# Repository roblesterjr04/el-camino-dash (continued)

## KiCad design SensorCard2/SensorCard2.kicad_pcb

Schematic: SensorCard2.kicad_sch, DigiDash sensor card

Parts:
C1, C5: 10u; C_0805_2012Metric
C2, C3, C4, C6, C7, C9, C10, C12, C13, C14, C15, C16, C21: 100n; C_0603_1608Metric
C8: 4.7u; C_0805_2012Metric
C17, C18, C19, C20: 10n; C_0603_1608Metric
C22: 100n; C_0805_2012Metric
C23, C24: 1n; C_0603_1608Metric
D1, D4, D5, D6, D7, D8, D9, D10: BAT54S; SOT-23
D2: BAT42W; D_SOD-123
D3: green; LED_0603_1608Metric
D11: 1N4148W; D_SOD-123
F1, F2, F3: PTC 0.1A; Fuse_1206_3216Metric
J1: DigiDash slot; PinHeader_2x15_P2.54mm_Horizontal
J2: Senders; JST_PH_S12B-PH-K_1x12_P2.00mm_Horizontal
J3: Speed; JST_PH_S4B-PH-K_1x04_P2.00mm_Horizontal
J4: Tach; Molex_Micro-Fit_3.0_43650-0200_1x02_P3.00mm_Horizontal
J5: RPM select; PinHeader_2x02_P2.54mm_Vertical
J6: SWD; PinHeader_1x05_P2.54mm_Horizontal
J7: Debug serial; PinHeader_1x06_P2.54mm_Horizontal
J8: Sensor serial out; PinHeader_1x03_P2.54mm_Horizontal
JP1: 5V / 12V; SolderJumper-3_P1.3mm_Bridged12_RoundedPad1.0x1.5mm
JP2: FUEL PU / PD; SolderJumper-3_P1.3mm_Bridged12_RoundedPad1.0x1.5mm
JP3: ETEMP PU / PD; SolderJumper-3_P1.3mm_Bridged12_RoundedPad1.0x1.5mm
JP4: OILP PU / PD; SolderJumper-3_P1.3mm_Bridged12_RoundedPad1.0x1.5mm
JP5: AMB PU / PD; SolderJumper-3_P1.3mm_Bridged12_RoundedPad1.0x1.5mm
JP6: FUEL 100; SolderJumper-2_P1.3mm_Bridged_RoundedPad1.0x1.5mm
JP7: FUEL 220; SolderJumper-2_P1.3mm_Open_RoundedPad1.0x1.5mm
JP8: FUEL 470; SolderJumper-2_P1.3mm_Open_RoundedPad1.0x1.5mm
JP9: ETEMP 220; SolderJumper-2_P1.3mm_Open_RoundedPad1.0x1.5mm
JP10: ETEMP 1k; SolderJumper-2_P1.3mm_Bridged_RoundedPad1.0x1.5mm
JP11: ETEMP 10k; SolderJumper-2_P1.3mm_Open_RoundedPad1.0x1.5mm
JP12: OILP 220; SolderJumper-2_P1.3mm_Bridged_RoundedPad1.0x1.5mm
JP13: OILP 1k; SolderJumper-2_P1.3mm_Open_RoundedPad1.0x1.5mm
JP14: OILP 100k; SolderJumper-2_P1.3mm_Open_RoundedPad1.0x1.5mm
JP15: AMB 10k; SolderJumper-2_P1.3mm_Open_RoundedPad1.0x1.5mm
JP16: AMB 100k; SolderJumper-2_P1.3mm_Bridged_RoundedPad1.0x1.5mm
R1: 33k; R_0603_1608Metric
R2, R15, R16, R18, R25, R29, R31, R33, R35, R37, R40, R41, R42: 10k; R_0603_1608Metric
R3, R5, R28, R30: 100k; R_0603_1608Metric
R4, R45: 22k; R_0603_1608Metric
R6: 47k; R_0603_1608Metric
R7, R8, R14, R24, R27, R46: 1k; R_0603_1608Metric
R9, R10: 4.7k; R_0603_1608Metric
R11, R12, R13: 100; R_0603_1608Metric
R17, R19: 15k; R_0603_1608Metric
R20: 100; R_2010_5025Metric
R21, R23, R26: 220; R_1206_3216Metric
R22: 470; R_0805_2012Metric
R32, R34, R36, R38: 20k; R_0603_1608Metric; not fitted
R39: 39k; R_0603_1608Metric
R43, R44: 4.7k; R_1206_3216Metric
U1: STM32G0B1KBU6; QFN-32-1EP_5x5mm_P0.5mm_EP3.45x3.45mm
U3: TJA1051T/3; SOIC-8_3.9x4.9mm_P1.27mm
U4: MB85RC256V; SOIC-8_3.9x4.9mm_P1.27mm
U5: PC817; SMDIP-4_W7.62mm
U6: AP2112K-3.3; SOT-23-5
U7: SN74LVC1T45; SOT-363_SC-70-6
Y1: 8MHz; Oscillator_SMD_Abracon_ASE-4Pin_3.2x2.5mm

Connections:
+3V3: C5.1, C6.1, C7.1, C8.1, C10.1, C13.1, C14.1, C15.1, D1.2 (K), D4.2 (K), D5.2 (K), D6.2 (K), D7.2 (K), D8.2 (K), D9.2 (K), D10.2 (K), J6.1, JP2.1 (A), JP3.1 (A), JP4.1 (A), JP5.1 (A), R9.1, R10.1, R15.1, R41.1, R45.1, U1.4 (VDD), U3.5 (Vio), U4.8 (VCC), U6.5 (VOUT), U7.1 (VCCA), U7.5 (DIR), Y1.1 (EN), Y1.4 (Vdd)
+5V: C1.1, C2.1, C12.1, C16.1, F1.1, F2.1, J1.1, J1.2, JP1.1 (A), U3.3 (VDD), U6.1 (VIN), U6.3 (EN), U7.6 (VCCB)
/ALT_L: C21.1, D8.3 (COM), R39.2, R40.1, U1.13 (PA6)
/ALT_L_IN: J2.11, R39.1
/AMB_TEMP: J2.9, R29.2, R30.2, R37.1
/AMB_TEMP_10K: JP15.2 (B), R29.1
/AMB_TEMP_100K: JP16.2 (B), R30.1
/AMB_TEMP_ADC: C20.1, D7.3 (COM), R37.2, R38.1, U1.12 (PA5)
/AMB_TEMP_BANK: JP5.2 (C), JP15.1 (A), JP16.1 (A)
/BATT_SENSE: C4.1, R3.2, R4.1, U1.14 (PA7)
/CANH: J1.5, U3.7 (CANH)
/CANL: J1.6, U3.6 (CANL)
/CAN_RX: R8.2, U1.22 (PA9/PA11)
/CAN_RXD: R8.1, U3.4 (RXD)
/CAN_TXD: U1.23 (PA10/PA12), U3.1 (TXD)
/DBG_RX: R11.2, U1.21 (PA10/UCPD1_DBCC2)
/DBG_TX: R12.1, U1.19 (PA9/UCPD1_DBCC1)
/ENGINE_TEMP: J2.3, R23.2, R24.2, R25.2, R33.1
/ENGINE_TEMP_1K: JP10.2 (B), R24.1
/ENGINE_TEMP_10K: JP11.2 (B), R25.1
/ENGINE_TEMP_220: JP9.2 (B), R23.1
/ENGINE_TEMP_ADC: C18.1, D5.3 (COM), R33.2, R34.1, U1.8 (PA1)
/ENGINE_TEMP_BANK: JP3.2 (C), JP9.1 (A), JP10.1 (A), JP11.1 (A)
/ENGINE_TEMP_VIN: F1.2, J2.4, R16.1
/FTDI_RXD: J7.5, R12.2
/FTDI_TXD: J7.4, R11.1
/FUEL: J2.1, R20.2, R21.2, R22.2, R31.1
/FUEL_100: JP6.2 (B), R20.1
/FUEL_220: JP7.2 (B), R21.1
/FUEL_470: JP8.2 (B), R22.1
/FUEL_ADC: C17.1, D4.3 (COM), R31.2, R32.1, U1.7 (PA0)
/FUEL_BANK: JP2.2 (C), JP6.1 (A), JP7.1 (A), JP8.1 (A)
/HSE_IN: U1.2 (PC14), Y1.3 (OUT)
/I2C_SCL: R10.2, U1.30 (PB6), U4.6 (SCL)
/I2C_SDA: R9.2, U1.31 (PB7), U4.5 (SDA)
/IGN_SENSE: C3.1, D1.3 (COM), R1.2, R2.1, U1.16 (PB1)
/LED_K: D3.1 (K), R7.1
/NRST: C9.1, J6.4, U1.6 (PF2)
/OIL_PRESSURE: J2.6, R26.2, R27.2, R28.2, R35.1
/OIL_PRESSURE_1K: JP13.2 (B), R27.1
/OIL_PRESSURE_100K: JP14.2 (B), R28.1
/OIL_PRESSURE_220: JP12.2 (B), R26.1
/OIL_PRESSURE_ADC: C19.1, D6.3 (COM), R35.2, R36.1, U1.11 (PA4)
/OIL_PRESSURE_BANK: JP4.2 (C), JP12.1 (A), JP13.1 (A), JP14.1 (A)
/OIL_PRESSURE_VIN: F2.2, J2.7, R18.1
/PRESS_MON: R18.2, R19.1, U1.1 (PB9)
/PWR_HOLD: D2.2 (A), R5.1, U1.26 (PA15)
/RPM_SEL_A: J5.2, U1.20 (PC6)
/RPM_SEL_B: J5.4, U1.27 (PB3)
/SENS_RX2: R14.2, R15.2, U1.10 (PA3)
/SENS_TX2: U1.9 (PA2), U7.3 (A)
/SER_IN: J8.3, R14.1
/SER_OUT: J8.2, R13.2
/SER_OUT_5V: R13.1, U7.4 (B)
/SLOT_12V: J1.8, JP1.3 (B), R1.1
/SLOT_BATT: J1.10, R3.1
/SPEED: J3.2, R41.2, R42.1
/SPEED_SIG: C23.1, D10.3 (COM), R42.2, U1.28 (PB4)
/SPEED_VIN: C22.1, F3.2, J3.1
/SPEED_VSEL: F3.1, JP1.2 (C)
/STATUS_LED: D3.2 (A), U1.29 (PB5)
/SWCLK: J6.3, U1.25 (PA14)
/SWDIO: J6.2, U1.24 (PA13)
/TACH: J4.1, R43.1
/TACH_LED: D11.1 (K), R44.2, U5.1
/TACH_OC: R45.2, R46.1, U5.4
/TACH_R: R43.2, R44.1
/TACH_SIG: C24.1, R46.2, U1.18 (PA8)
/TEMP_MON: R16.2, R17.1, U1.17 (PB2)
/WAKE: D2.1 (K), J1.12, R6.1
/WAKE_SENSE: D9.3 (COM), R6.2, U1.15 (PB0)
GND: C1.2, C2.2, C3.2, C4.2, C5.2, C6.2, C7.2, C8.2, C9.2, C10.2, C12.2, C13.2, C14.2, C15.2, C16.2, C17.2, C18.2, C19.2, C20.2, C21.2, C22.2, C23.2, C24.2, D1.1 (A), D4.1 (A), D5.1 (A), D6.1 (A), D7.1 (A), D8.1 (A), D9.1 (A), D10.1 (A), D11.2 (A), J1.3, J1.4, J1.7, J1.19, J1.20, J2.2, J2.5, J2.8, J2.10, J2.12, J3.3, J3.4, J4.2, J5.1, J5.3, J6.5, J7.1, J7.2, J8.1, JP2.3 (B), JP3.3 (B), JP4.3 (B), JP5.3 (B), R2.2, R4.2, R5.2, R7.2, R17.2, R19.2, R32.2, R34.2, R36.2, R38.2, R40.2, U1.5 (VSS), U1.33 (VSS), U3.2 (VSS), U3.8 (STBY), U4.1 (A0), U4.2 (A1), U4.3 (A2), U4.4 (GND), U4.7 (WP), U5.2, U5.3, U6.2 (GND), U7.2 (GND), Y1.2 (GND)

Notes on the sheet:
SENSOR CARD rev B - the DigiDash sensor pack on a slot card: STM32G0B1KBU6 (FDCAN) + TJA1051 (CAN node 0x04, fixed) + FRAM odometer
Card for a DigiDash slot, 80 x 60 mm, standing on edge (docs/hardware/accessory_ports.md). Any slot but slot 1 (kept for tall parts). Sender, speed and tach connectors on the top edge; SWD, debug serial and the sensor serial out on the left edge. Rev B (2026-10-26) replaces rev A's ATmega2560 + MCP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
SLOT (J1, right-angle 2x15 on the bottom edge): 5 V, GND, CAN, switched 12 V (ignition sense, speed sensor feed), constant 12 V (battery sense), WAKE (hold the 5 V rail after key-off)
IGN: slot switched 12 V (on with the key) -> 33k / 10k (14.5 V -> 3.4 V, clamped; HIGH from about 6 V), on an ADC pin. BATT: slot constant 12 V -> 100k / 22k (16 V -> 2.9 V) on ADC IN7. WAKE: PWR_HOLD (3.3 V GPIO) -> Schottky -> slot WAKE: keeps the main board's 5 V on after key-off. WAKE -> 47k ->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
POWER: slot +5 V -> AP2112K-3.3 (600 mA): the MCU, the transceiver VIO, the FRAM, the sender pull-up banks (up to about 130 mA with every bank shorted), the clamps. The sender feeds (ETEMP V, OILP V) and the speed sensor stay on 5 V.
MCU: STM32G0B1KBU6 (UFQFPN-32), 3.3 V, 8 MHz HSE from an oscillator in bypass (CAN bit timing). Every I/O pin is used: pin map in SensorCard2/README.md
PA11 / PA12 FDCAN1 RX / TX (AF3). PA9 / PA10 USART1 TX / RX (AF1): debug serial J7 (also the ROM bootloader). PA2 / PA3 USART2 TX / RX (AF1): sensor serial J8 (TX through a 3.3 -> 5 V level shifter). PB6 / PB7 I2C1 SCL / SDA (AF6): FRAM. PA8 TIM1_CH1 (AF2): tach. PB4 TIM3_CH1 (AF1): speed. ADC: PA0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
PROGRAMMING AND SERIAL (right angle, left edge): J6 SWD (ST-Link), J7 debug serial (USART1, the FTDI pinout, 3.3 V), J8 sensor serial out (USART2: 5 V TX through the level shifter; an optional jumper wire to the main board J27, which fans it out to the screens)
SENDERS (J2, JST PH 12 pin, top edge). Each channel: a topology jumper (pull-up to +3V3 or pull-down to GND) feeding a bank of resistors, each behind its own solder jumper. Bridge one value (two give them in parallel). 10k + 10 nF into the ADC, clamped to 3.3 V.
As delivered: every channel pull-up (topology jumper 1-2); FUEL 100R (the factory 0-30R sender), ETEMP 1k, OILP 220R, AMB 100k bridged. The pull-ups come from +3V3 and the ADC reference is the same 3.3 V, so a resistive sender reads ratiometrically, as rev A did at 5 V: the same counts. Pull-down m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
SPEED (J3, JST PH 4, top edge): a hall / drop-in cable-replacement sensor. JP1 picks its supply: 5 V (1-2, as delivered) or the slot switched 12 V (2-3). Open-collector or push-pull output up to 12 V.
TACH (J4, Micro-Fit 3.0, 2 pin, top edge, its own connector: coil-negative kick is hundreds of volts). PC817 isolation; keep the TACH net clear of everything else up to the two 1206 resistors.

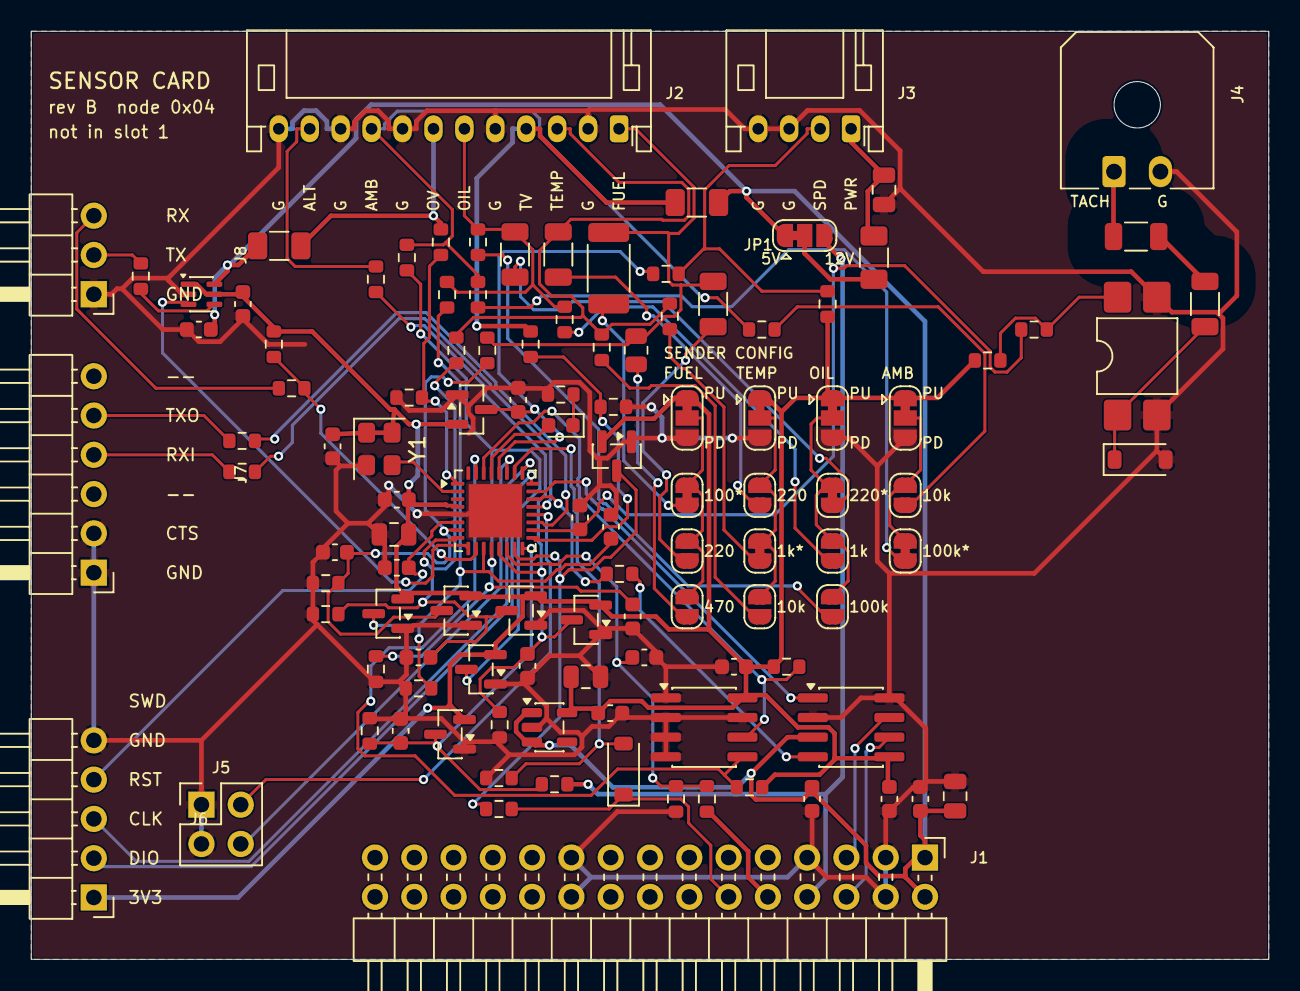
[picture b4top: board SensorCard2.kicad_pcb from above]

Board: 2 copper layers, 80.0 x 60.0 mm, 114 parts (0 on the bottom side), 72 nets.

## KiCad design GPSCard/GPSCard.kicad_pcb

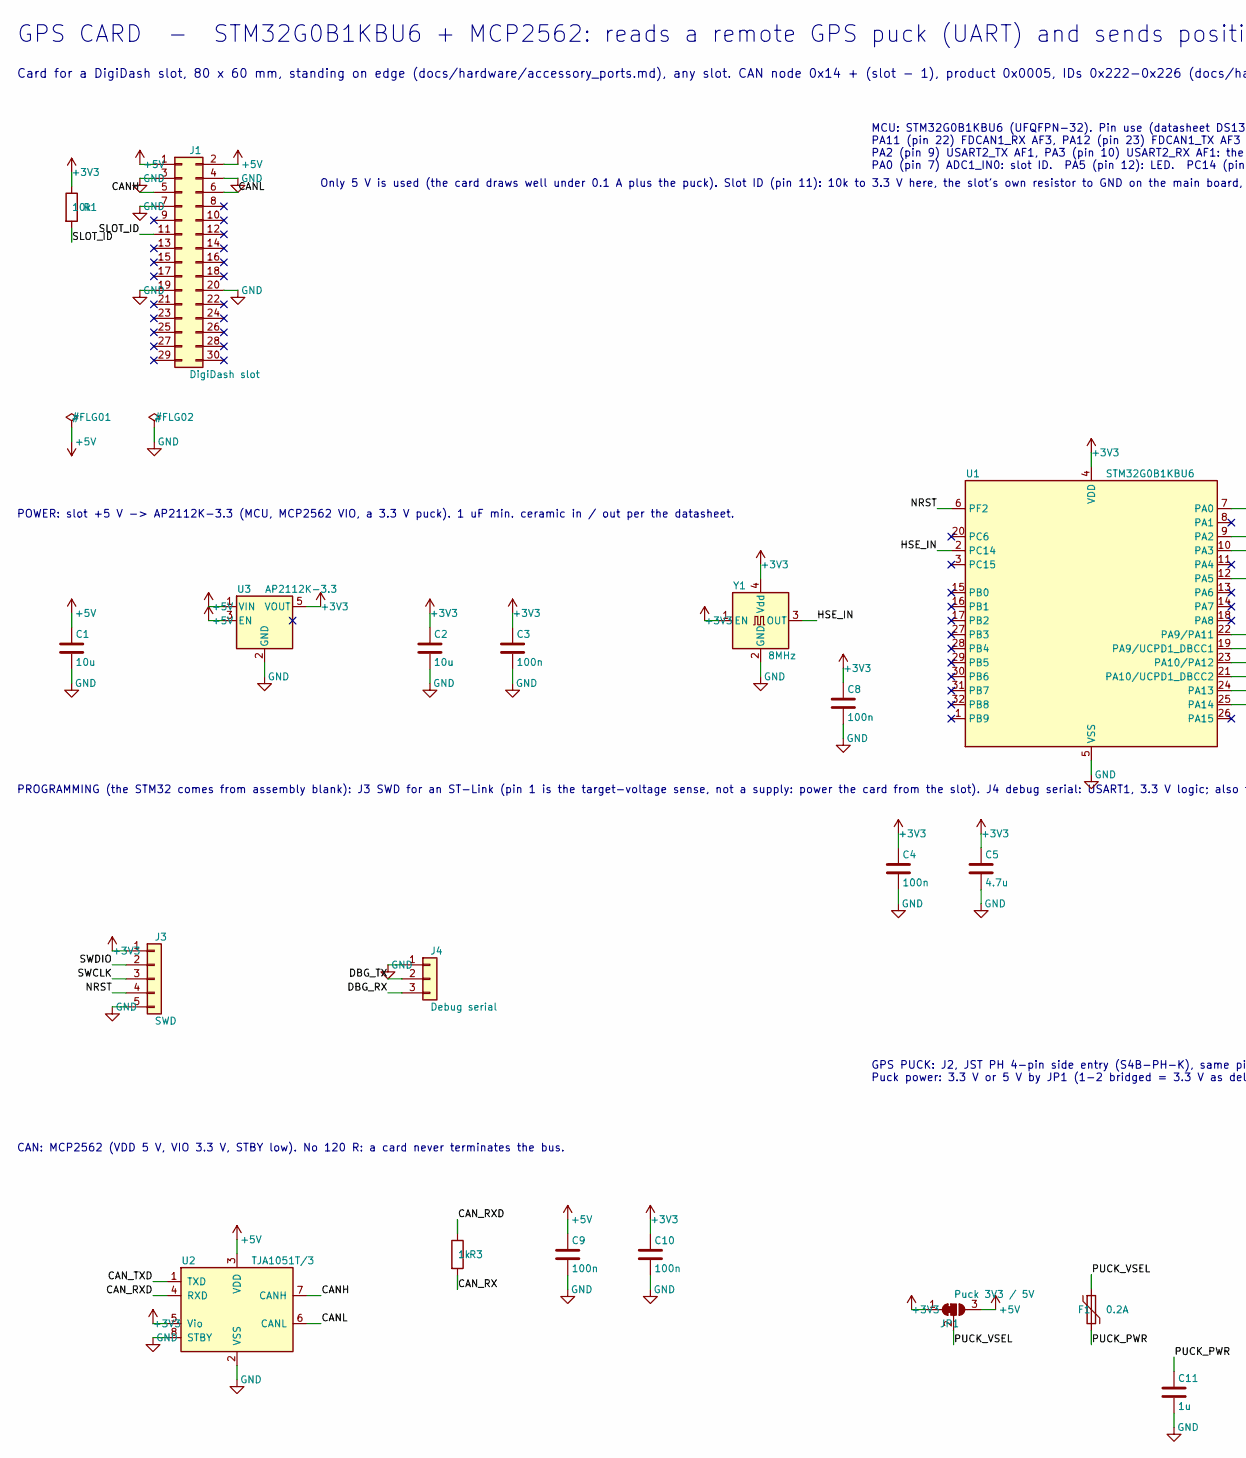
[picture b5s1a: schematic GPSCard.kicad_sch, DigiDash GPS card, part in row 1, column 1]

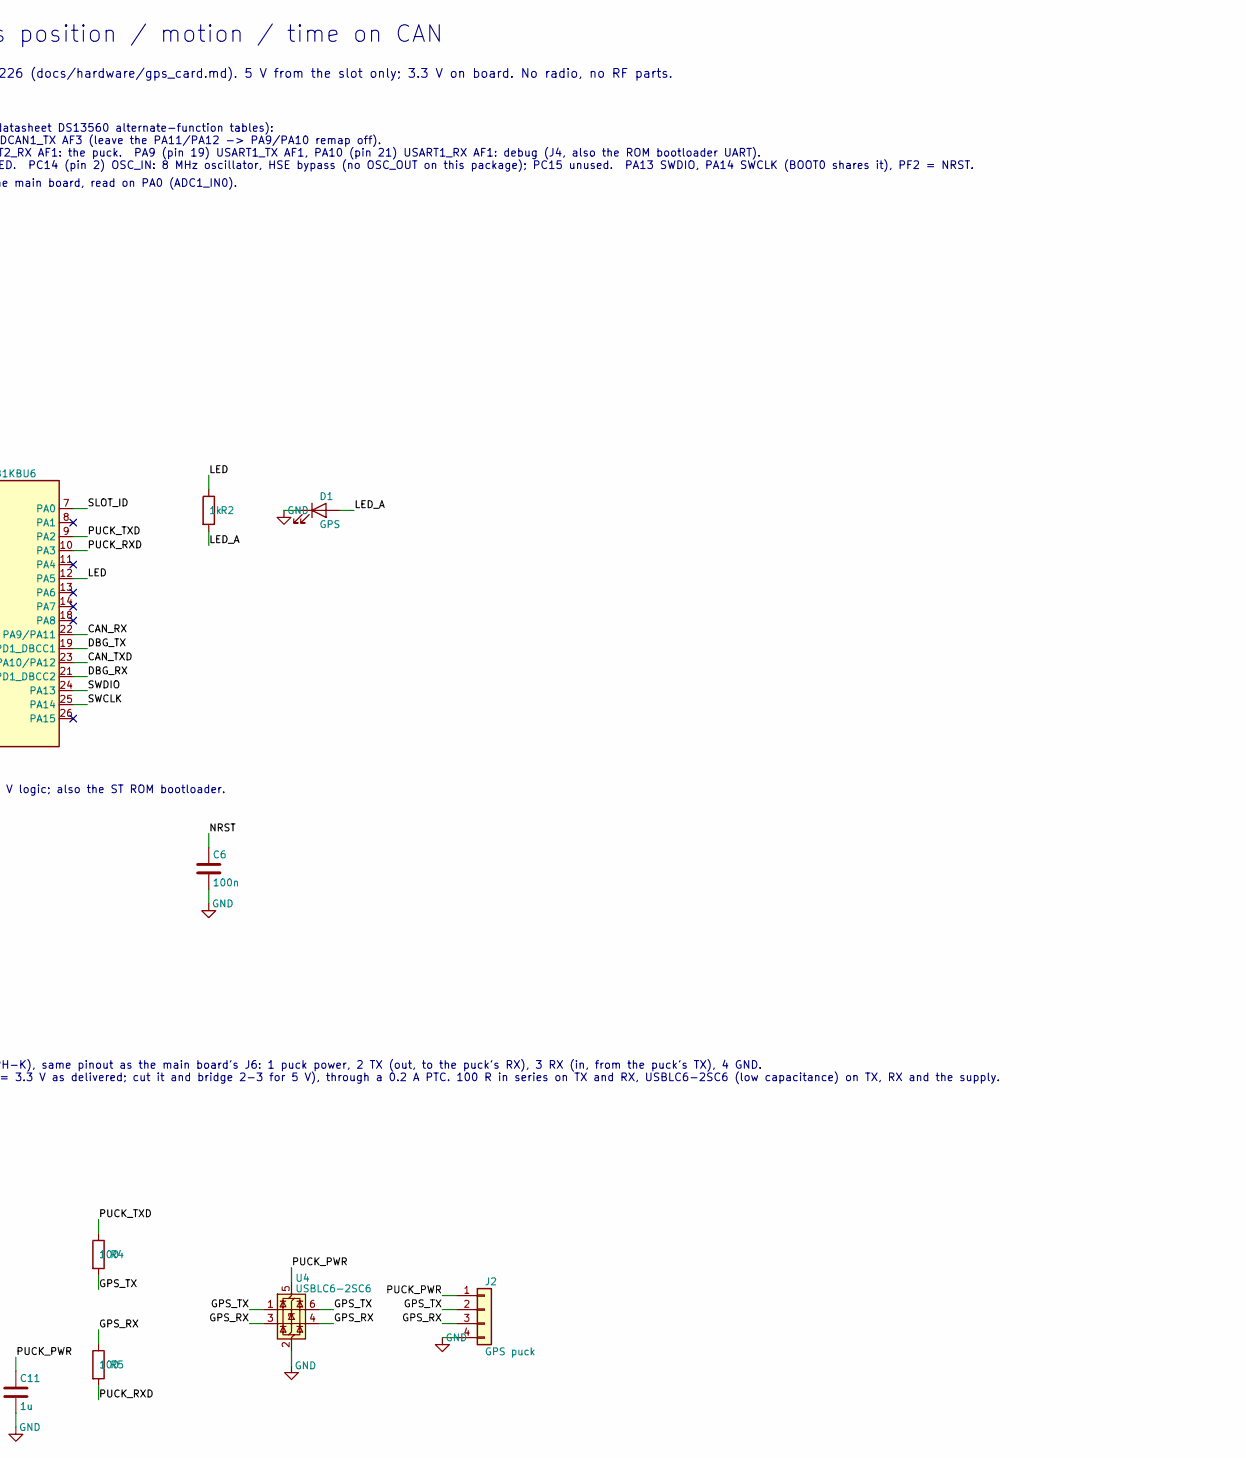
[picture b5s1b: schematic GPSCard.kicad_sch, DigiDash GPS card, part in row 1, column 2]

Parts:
C1, C2: 10u; C_0805_2012Metric
C3, C4, C6, C8, C9, C10: 100n; C_0603_1608Metric
C5: 4.7u; C_0603_1608Metric
C11: 1u; C_0603_1608Metric
D1: GPS; LED_0603_1608Metric
F1: 0.2A; Fuse_1206_3216Metric
J1: DigiDash slot; PinHeader_2x15_P2.54mm_Horizontal
J2: GPS puck; JST_PH_S4B-PH-K_1x04_P2.00mm_Horizontal
J3: SWD; PinHeader_1x05_P2.54mm_Horizontal
J4: Debug serial; PinHeader_1x03_P2.54mm_Horizontal
JP1: Puck 3V3 / 5V; SolderJumper-3_P1.3mm_Bridged12_RoundedPad1.0x1.5mm
R1: 10k; R_0603_1608Metric
R2, R3: 1k; R_0603_1608Metric
R4, R5: 100; R_0603_1608Metric
U1: STM32G0B1KBU6; QFN-32-1EP_5x5mm_P0.5mm_EP3.45x3.45mm
U2: TJA1051T/3; SOIC-8_3.9x4.9mm_P1.27mm
U3: AP2112K-3.3; SOT-23-5
U4: USBLC6-2SC6; SOT-23-6
Y1: 8MHz; Oscillator_SMD_Abracon_ASE-4Pin_3.2x2.5mm

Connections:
+3V3: C2.1, C3.1, C4.1, C5.1, C8.1, C10.1, J3.1, JP1.1 (A), R1.1, U1.4 (VDD), U2.5 (Vio), U3.5 (VOUT), Y1.1 (EN), Y1.4 (Vdd)
+5V: C1.1, C9.1, J1.1, J1.2, JP1.3 (B), U2.3 (VDD), U3.1 (VIN), U3.3 (EN)
/CANH: J1.5, U2.7 (CANH)
/CANL: J1.6, U2.6 (CANL)
/CAN_RX: R3.2, U1.22 (PA9/PA11)
/CAN_RXD: R3.1, U2.4 (RXD)
/CAN_TXD: U1.23 (PA10/PA12), U2.1 (TXD)
/DBG_RX: J4.3, U1.21 (PA10/UCPD1_DBCC2)
/DBG_TX: J4.2, U1.19 (PA9/UCPD1_DBCC1)
/GPS_RX: J2.3, R5.1, U4.3 (I/O2), U4.4 (I/O2)
/GPS_TX: J2.2, R4.2, U4.1 (I/O1), U4.6 (I/O1)
/HSE_IN: U1.2 (PC14), Y1.3 (OUT)
/LED: R2.1, U1.12 (PA5)
/LED_A: D1.2 (A), R2.2
/NRST: C6.1, J3.4, U1.6 (PF2)
/PUCK_PWR: C11.1, F1.2, J2.1, U4.5 (VBUS)
/PUCK_RXD: R5.2, U1.10 (PA3)
/PUCK_TXD: R4.1, U1.9 (PA2)
/PUCK_VSEL: F1.1, JP1.2 (C)
/SLOT_ID: J1.11, R1.2, U1.7 (PA0)
/SWCLK: J3.3, U1.25 (PA14)
/SWDIO: J3.2, U1.24 (PA13)
GND: C1.2, C2.2, C3.2, C4.2, C5.2, C6.2, C8.2, C9.2, C10.2, C11.2, D1.1 (K), J1.3, J1.4, J1.7, J1.19, J1.20, J2.4, J3.5, J4.1, U1.5 (VSS), U1.33 (VSS), U2.2 (VSS), U2.8 (STBY), U3.2 (GND), U4.2 (GND), Y1.2 (GND)

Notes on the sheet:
GPS CARD - STM32G0B1KBU6 + MCP2562: reads a remote GPS puck (UART) and sends position / motion / time on CAN
Card for a DigiDash slot, 80 x 60 mm, standing on edge (docs/hardware/accessory_ports.md), any slot. CAN node 0x14 + (slot - 1), product 0x0005, IDs 0x222-0x226 (docs/hardware/gps_card.md). 5 V from the slot only; 3.3 V on board. No radio, no RF parts.
Only 5 V is used (the card draws well under 0.1 A plus the puck). Slot ID (pin 11): 10k to 3.3 V here, the slot's own resistor to GND on the main board, read on PA0 (ADC1_IN0).
POWER: slot +5 V -> AP2112K-3.3 (MCU, MCP2562 VIO, a 3.3 V puck). 1 uF min. ceramic in / out per the datasheet.
MCU: STM32G0B1KBU6 (UFQFPN-32). Pin use (datasheet DS13560 alternate-function tables): PA11 (pin 22) FDCAN1_RX AF3, PA12 (pin 23) FDCAN1_TX AF3 (leave the PA11/PA12 -> PA9/PA10 remap off). PA2 (pin 9) USART2_TX AF1, PA3 (pin 10) USART2_RX AF1: the puck. PA9 (pin 19) USART1_TX AF1, PA10 (pin 21) USA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
PROGRAMMING (the STM32 comes from assembly blank): J3 SWD for an ST-Link (pin 1 is the target-voltage sense, not a supply: power the card from the slot). J4 debug serial: USART1, 3.3 V logic; also the ST ROM bootloader.
CAN: MCP2562 (VDD 5 V, VIO 3.3 V, STBY low). No 120 R: a card never terminates the bus.
GPS PUCK: J2, JST PH 4-pin side entry (S4B-PH-K), same pinout as the main board's J6: 1 puck power, 2 TX (out, to the puck's RX), 3 RX (in, from the puck's TX), 4 GND. Puck power: 3.3 V or 5 V by JP1 (1-2 bridged = 3.3 V as delivered; cut it and bridge 2-3 for 5 V), through a 0.2 A PTC. 100 R in se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

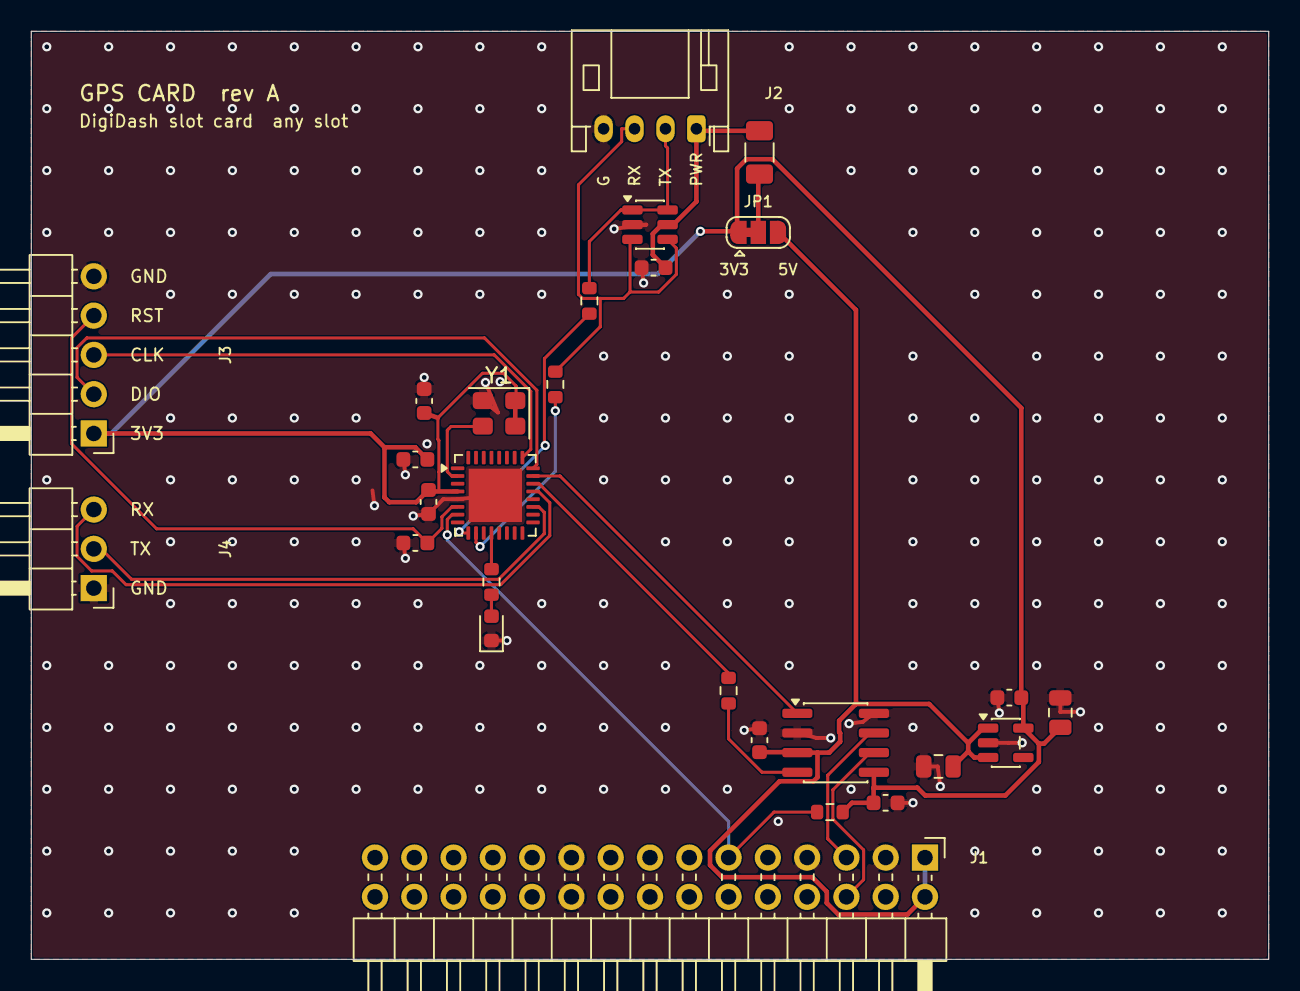
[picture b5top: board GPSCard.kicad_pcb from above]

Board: 2 copper layers, 80.0 x 60.0 mm, 27 parts (0 on the bottom side), 23 nets.

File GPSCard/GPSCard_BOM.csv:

Qty,Designators,Manufacturer part,Description,Package,Type,Side,Notes
2,C1 C2,Samsung CL21A106KPFNNNE,10u: Capacitor 10u X5R 10 V (5 V in / 3.3 V out of U3),0805,SMD,Top,
6,C3 C4 C6 C8 C9 C10,Samsung CL10B104KB8NNNC,100n: Capacitor 100n X7R 50 V,0603,SMD,Top,
1,C5,Samsung CL10A475KP8NNNC,4.7u: Capacitor 4.7u X5R 10 V (MCU VDD),0603,SMD,Top,
1,C11,Samsung CL10B105KO8NNNC,1u: Capacitor 1u X7R 16 V (puck supply),0603,SMD,Top,
1,D1,Lite-On LTST-C191KGKT,"GPS: status LED, green",0603,SMD,Top,Cathode = pad 1 (to GND)
1,F1,Bourns MF-NSMF020-2,"0.2A: PTC resettable fuse, 0.2 A hold (puck supply)",1206,SMD,Top,
1,J1,Sullins PRPC015DBAN-M71RC,"DigiDash slot: pin header 2 x 15, 2.54 mm, right angle",THT,THT,Top,"Same part as the audio card. Any 2 x 15 2.54 mm right-angle male header; on the bottom edge, pins pointing off the board"
1,J2,JST S4B-PH-K-S,"GPS puck: JST PH 4-pin, side entry (1 power, 2 TX, 3 RX, 4 GND)",THT,THT,Top,Plug opening faces off the top edge
1,J3,Sullins PRPC005SBAN-M71RC,"SWD: pin header 1 x 5, 2.54 mm, right angle (3V3 sense, SWDIO, SWCLK, NRST, GND)",THT,THT,Top,"Left edge, pins pointing off the board. Any 1 x 5 2.54 mm right-angle header"
1,J4,Sullins PREC003SBAN-M71RC,"Debug serial: pin header 1 x 3, 2.54 mm, right angle (GND, TX, RX)",THT,THT,Top,"Left edge, pins pointing off the board. Any 1 x 3 2.54 mm right-angle header"
1,R1,Yageo RC0603FR-0710KL,10k: Resistor 10k 1% (slot ID pull-up),0603,SMD,Top,
2,R2 R3,Yageo RC0603FR-071KL,1k: Resistor 1k 1% (LED; CAN RXD series),0603,SMD,Top,
2,R4 R5,Yageo RC0603FR-07100RL,100: Resistor 100 1% (puck TX / RX series),0603,SMD,Top,
1,U1,STMicroelectronics STM32G0B1KBU6,"MCU: Cortex-M0+ 64 MHz, 128 KB flash, 144 KB RAM, FDCAN",UFQFPN-32 5 x 5 mm (exposed pad),SMD,Top,Not the KBU6N (different pinout). Arrives blank: flashed over J3 after assembly. Exposed pad = GND
1,U2,NXP TJA1051T/3/1J,"CAN FD transceiver, VDD 5 V, VIO 3.3 V",SOIC-8,SMD,Top,
1,U3,Diodes Inc AP2112K-3.3TRG1,LDO 3.3 V 600 mA,SOT-23-5,SMD,Top,
1,U4,STMicroelectronics USBLC6-2SC6,"ESD array (puck TX, RX, supply)",SOT-23-6,SMD,Top,
1,Y1,YXC (Yangxing) OT32258MJBA4SL,"8 MHz CMOS oscillator, 1.8-3.3 V, +-10 ppm, +-20 ppm over -40 to +85 C, 45-55 % duty, tri-state pin 1",SMD3225-4P (3.2 x 2.5 mm),SMD,Top,"LCSC C717687. An oscillator, not a crystal: the 32-pin STM32G0B1 has no OSC_OUT, so PC14 takes a clock in HSE bypass. Pinout (YXC YSO110TR datasheet): 1 tri-state (tied to 3V3), 2 GND, 3 OUT, 4 VDD"
1,JP1,Solder jumper (PCB),"Puck 3V3 / 5V: 3-pad solder jumper, 1-2 bridged by a copper trace as delivered (3.3 V)",PCB,PCB,Top,"Not placed. For 5 V: cut the 1-2 trace, bridge 2-3"
